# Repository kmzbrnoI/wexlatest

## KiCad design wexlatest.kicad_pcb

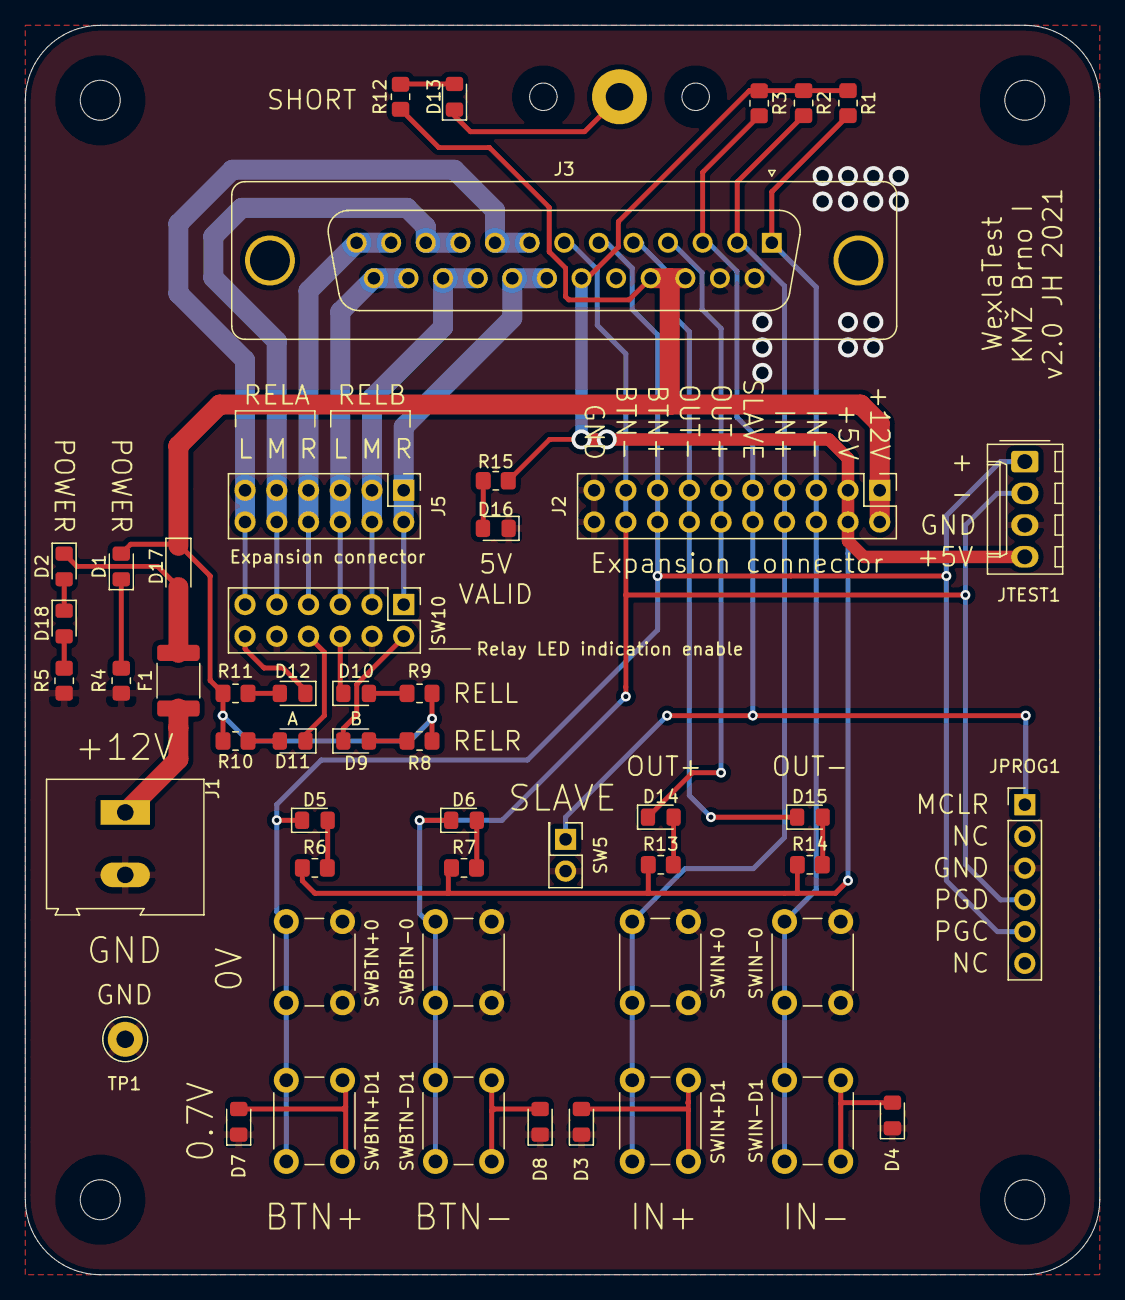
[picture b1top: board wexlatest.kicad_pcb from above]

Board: 2 copper layers, 86.0 x 100.0 mm, 58 parts (0 on the bottom side), 40 nets.

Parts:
D1, D16: GR; LED_0805_2012Metric_Pad1.15x1.40mm_HandSolder
D2, D13: RED; LED_0805_2012Metric_Pad1.15x1.40mm_HandSolder
D3, D4, D7, D8, D18: 1N4148; D_0805_2012Metric_Pad1.15x1.40mm_HandSolder
D5, D6: YEL; LED_0805_2012Metric_Pad1.15x1.40mm_HandSolder
D9, D10, D11, D12: BLUE; LED_0805_2012Metric_Pad1.15x1.40mm_HandSolder
D14, D15: WH; LED_0805_2012Metric_Pad1.15x1.40mm_HandSolder
D17: 1N4007; D_SOD-123
F1: Polyfuse; R_1812_4532Metric_Pad1.30x3.40mm_HandSolder
H1: MountingHole_Pad; MountingHole_2.2mm_M2_Pad
H2, H3, H4, H5: MountingHole; MountingHole_3.2mm_M3
H6, H7: MountingHole; MountingHole_2.2mm_M2
J1: Screw_Terminal_01x02; TerminalBlock_Altech_AK300-2_P5.00mm
J2: Conn_02x10_Odd_Even; PinHeader_2x10_P2.54mm_Vertical
J3: DB25_Female; DSUB-25_Female_Vertical_P2.77x2.84mm_MountingHoles
J5: Conn_02x06_Odd_Even; PinHeader_2x06_P2.54mm_Vertical
JPROG1: PROG; PinHeader_1x06_P2.54mm_Vertical
JTEST1: Conn_01x04; Molex_KK-254_AE-6410-04A_1x04_P2.54mm_Vertical
R1, R2, R3: 10k; R_0805_2012Metric_Pad1.20x1.40mm_HandSolder
R4, R5, R6, R7, R8, R9, R10, R11, R12, R13, R14, R15: 1k; R_0805_2012Metric_Pad1.20x1.40mm_HandSolder
SW5: SW_DIP_x01; PinHeader_2x01_P2.54mm_Vertical
SW10: SW_DIP_x06; PinHeader_2x06_P2.54mm_Vertical
SWBTN+0: SW_Push; SW_PUSH_6mm
SWBTN+D1: SW_Push; SW_PUSH_6mm
SWBTN-0: SW_Push; SW_PUSH_6mm
SWBTN-D1: SW_Push; SW_PUSH_6mm
SWIN+0: SW_Push; SW_PUSH_6mm
SWIN+D1: SW_Push; SW_PUSH_6mm
SWIN-0: SW_Push; SW_PUSH_6mm
SWIN-D1: SW_Push; SW_PUSH_6mm
TP1: TestPoint_Probe; TestPoint_Loop_D3.50mm_Drill1.4mm_Beaded

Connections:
+5V: J2.3, J2.4, J3.19, JTEST1.4, R1.1, R2.1, R3.1, R6.1, R7.1, R13.1, R14.1, R15.1
+12V: D1.2, D17.1, J2.1, J2.2, J3.16, J3.17, R8.2, R9.2, R10.2, R11.2, R12.1
BTN+|PGC: D5.1, J2.15, J2.16, J3.6, JPROG1.5, JTEST1.1, SWBTN+0.1, SWBTN+D1.1
BTN-|PGD: D6.1, J2.17, J2.18, J3.7, JPROG1.4, JTEST1.2, SWBTN-0.1, SWBTN-D1.1
GND: D3.1, D4.1, D7.1, D8.1, D16.1, J1.2, J2.19, J2.20, J3.14, J3.15, JPROG1.3, JTEST1.3, R4.2, R5.2, SW5.2, SW10.4, SW10.10, SWBTN+0.2, SWBTN-0.2, SWIN+0.2, SWIN-0.2, TP1.1
IN+: J2.7, J2.8, J3.2, R1.2, SWIN+0.1, SWIN+D1.1
IN-: J2.5, J2.6, J3.1, R2.2, SWIN-0.1, SWIN-D1.1
IN-SLAVE|MCLR: J2.9, J2.10, J3.3, JPROG1.1, R3.2, SW5.1
unnamed: D1.1, R4.1
unnamed: D3.2, SWIN+D1.2
unnamed: D4.2, SWIN-D1.2
unnamed: D5.2, R6.2
unnamed: D6.2, R7.2
unnamed: D7.2, SWBTN+D1.2
unnamed: D8.2, SWBTN-D1.2
unnamed: D9.1, SW10.2
unnamed: D9.2, R8.1
unnamed: D10.1, SW10.6
unnamed: D10.2, R9.1
unnamed: D11.1, SW10.8
unnamed: D11.2, R10.1
unnamed: D12.1, SW10.12
unnamed: D12.2, R11.1
unnamed: D13.1, H1.1
unnamed: D13.2, R12.2
unnamed: D14.2, R13.2
unnamed: D15.2, R14.2
unnamed: D16.2, R15.2
unnamed: D2.1, D17.2, F1.2
unnamed: D2.2, D18.1
unnamed: D18.2, R5.1
unnamed: F1.1, J1.1
OUT+: D14.1, J2.11, J2.12, J3.4
OUT-: D15.1, J2.13, J2.14, J3.5
RELAL: J3.8, J3.9, J5.11, J5.12, SW10.11
RELAM: J3.10, J3.11, J5.9, J5.10, SW10.9
RELAR: J3.12, J3.13, J5.7, J5.8, SW10.7
RELBL: J3.24, J3.25, J5.5, J5.6, SW10.5
RELBM: J3.22, J3.23, J5.3, J5.4, SW10.3
RELBR: J3.20, J3.21, J5.1, J5.2, SW10.1

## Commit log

2021-10-14 Add .gitignore.
2021-10-14 Add initial versio of schematics.
2021-11-07 Annotate parts, add footprints, check ERC.
2021-11-07 Add protection diodes.
2021-11-07 Add KK254 connector.
2021-11-07 Add initial PCB layout.
2021-11-08 PCB: add some wires
2021-11-09 PCB: trace all wires, first prototype.
2021-11-09 Add holes for mechanical test of turnout force.
2021-11-10 Add fab-creating Makefile.
2021-11-10 Add mounting holes clearences.
2021-11-10 Enlange filled zone.
2021-12-08 Fix bad relay polarity.
2021-12-08 Fix switched OUT+ & OUT-.
2021-12-16 Change fuse package to 1812.
